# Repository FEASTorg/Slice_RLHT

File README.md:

# Sice RLHT

Relay Heating Element Controller Slice for BREAD.

## Introduction

[Provide a brief introduction to the project, including the motivation and goals. Explain the significance and context of the research.]

## Project Overview

[Describe the project in more detail. This section can be split into subsections if necessary.]

## Installation

[Provide instructions for installing any necessary software or hardware components.]

## Usage

[Explain how to use the project. Include examples and screenshots if applicable.]

### Basic Usage

[Provide basic usage instructions.]

### Advanced Usage

[Provide advanced usage instructions, including any optional features or configurations.]

## Documentation

[Link to the detailed documentation if available. Provide instructions on how to access and navigate the documentation.]

## Contributing

[Explain how others can contribute to the project. Include guidelines for submitting issues, pull requests, and any coding standards.]

### Code of Conduct

[Link to the project's code of conduct if available.]

## License

[State the license under which the project is distributed. Include a link to the full license text.]

## Acknowledgements

[Acknowledge any contributors, collaborators, funding sources, or organizations that supported the project.]

## Contact

[Provide contact information for the project maintainer(s) or lead researcher(s). Include an email address or a link to a contact form.]

---

<div align="center">
  
</div>

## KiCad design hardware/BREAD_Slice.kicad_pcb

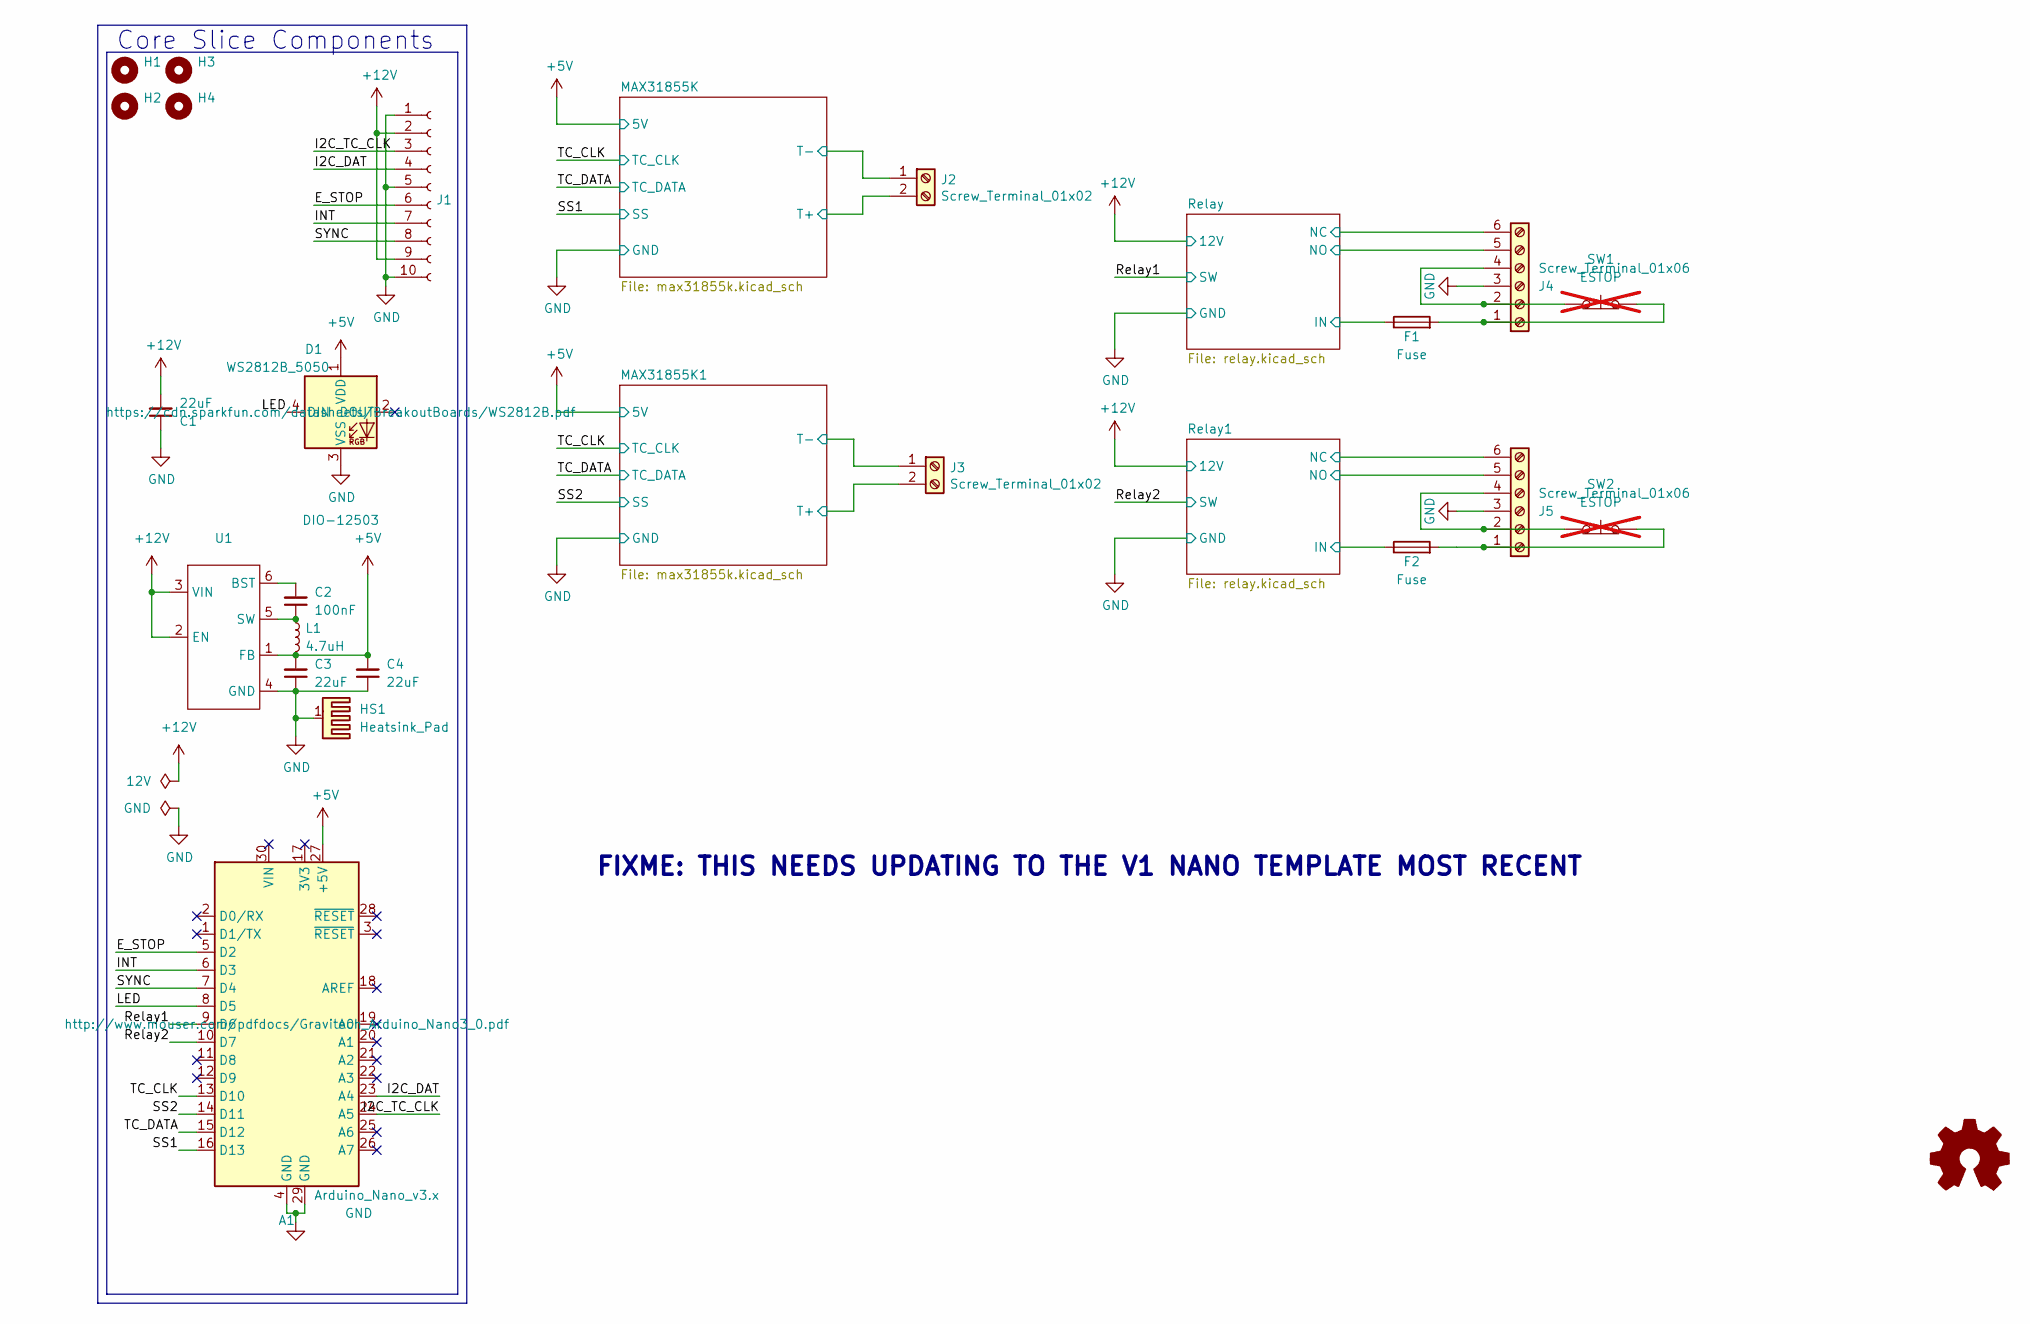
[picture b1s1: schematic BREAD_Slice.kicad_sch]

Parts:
A1: Arduino_Nano_v3.x; Arduino_Nano
C1, C3, C4: 22uF; C_1206_3216Metric
C2: 100nF; C_1206_3216Metric
D1: WS2812B_5050; WS2812-5050-4PIN
F1, F2: Fuse; Fuseholder_Clip-5x20mm_Bel_FC-203-22_Lateral_P17.80x5.00mm_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
H1, H2, H3, H4: MountingHole; MountingHole_5mm
HS1: Heatsink_Pad; Thermal_Pad
J1: Conn_01x10_Female; PinSocket_1x10_P2.54mm_Horizontal
J2, J3: Screw_Terminal_01x02; TerminalBlock_Phoenix_MPT-0,5-2-2.54_1x02_P2.54mm_Horizontal
J4, J5: Screw_Terminal_01x06; TerminalBlock_Phoenix_MKDS-1,5-6-5.08_1x06_P5.08mm_Horizont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
L1: 4.7uH; L_1210_3225Metric
SW1, SW2: ESTOP; not fitted
U1: SOIC_05WU-7_DIO

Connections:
+5V: A1.27 (+5V), C3.2, C4.2, D1.1 (VDD), L1.2, U1.1 (FB); also elsewhere on the board
+12V: C1.2, J1.2, J1.9, U1.2 (EN), U1.3 (VIN); also elsewhere on the board
/E_STOP: A1.5 (D2), J1.6
/I2C_DAT: A1.23 (A4), J1.4
/I2C_TC_CLK: A1.24 (A5), J1.3
/INT: A1.6 (D3), J1.7
/LED: A1.8 (D5), D1.4 (DIN)
/MAX31855K1/T+: J3.2; also elsewhere on the board
/MAX31855K1/T-: J3.1; also elsewhere on the board
/MAX31855K/T+: J2.2; also elsewhere on the board
/MAX31855K/T-: J2.1; also elsewhere on the board
/Relay1: A1.9 (D6); also elsewhere on the board
/Relay1/IN: F2.1; also elsewhere on the board
/Relay1/NC: J5.6; also elsewhere on the board
/Relay1/NO: J5.5; also elsewhere on the board
/Relay2: A1.10 (D7); also elsewhere on the board
/Relay/IN: F1.1; also elsewhere on the board
/Relay/NC: J4.6; also elsewhere on the board
/Relay/NO: J4.5; also elsewhere on the board
/SS1: A1.16 (D13); also elsewhere on the board
/SS2: A1.14 (D11); also elsewhere on the board
/SYNC: A1.7 (D4), J1.8
/TC_CLK: A1.13 (D10); also elsewhere on the board
/TC_DATA: A1.15 (D12); also elsewhere on the board
GND: A1.4 (GND), A1.29 (GND), C1.1, C3.1, C4.1, D1.3 (VSS), HS1.1, J1.1, J1.5, J1.10, J4.3, J5.3, U1.4 (GND); also elsewhere on the board
unnamed: F1.2, J4.1, SW1.2 (B)
unnamed: J4.2, J4.4, SW1.1 (A)
unnamed: F2.2, J5.1, SW2.2 (B)
unnamed: J5.2, J5.4, SW2.1 (A)
unnamed: C2.2, U1.6 (BST)
unnamed: C2.1, L1.1, U1.5 (SW)

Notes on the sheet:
FIXME: THIS NEEDS UPDATING TO THE V1 NANO TEMPLATE MOST RECENT
Core Slice Components

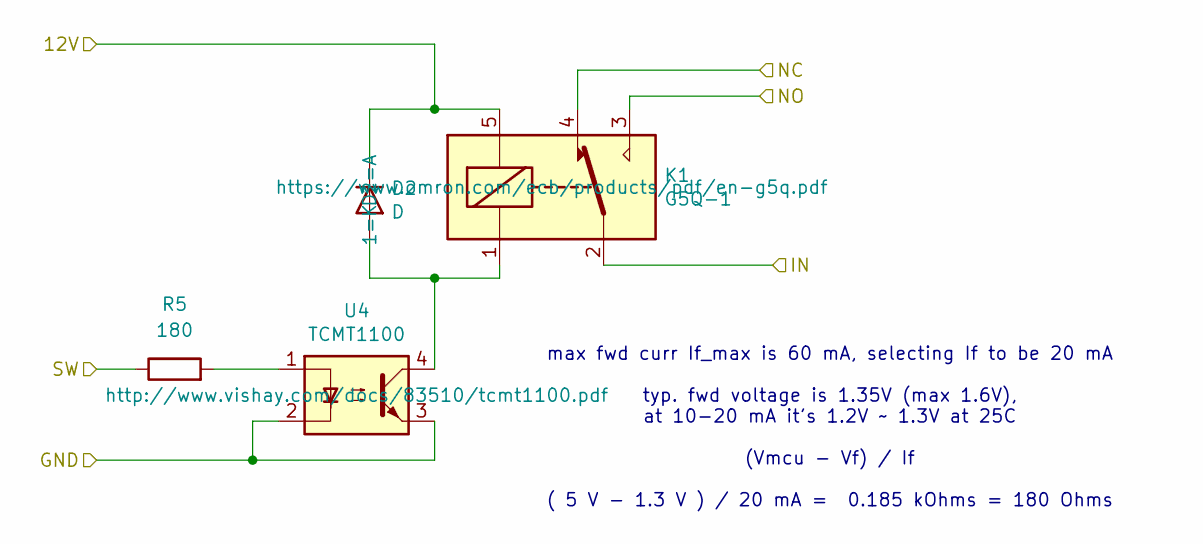
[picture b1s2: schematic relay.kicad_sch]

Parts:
D2: D; D_DO-35_SOD27_P7.62mm_Horizontal
K1: G5Q-1; Relay_SPDT_Omron-G5Q-1
R5: 180; R_1206_3216Metric_Pad1.30x1.75mm_HandSolder
U4: TCMT1100; SOP-4_4.4x2.6mm_P1.27mm

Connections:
+12V: D2.1 (K), K1.5; also elsewhere on the board
/Relay1: R5.1; also elsewhere on the board
/Relay/IN: K1.2; also elsewhere on the board
/Relay/NC: K1.4; also elsewhere on the board
/Relay/NO: K1.3; also elsewhere on the board
GND: U4.2, U4.3; also elsewhere on the board
unnamed: D2.2 (A), K1.1, U4.4
unnamed: R5.2, U4.1

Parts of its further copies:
D3: D; D_DO-35_SOD27_P7.62mm_Horizontal
K2: G5Q-1; Relay_SPDT_Omron-G5Q-1
R6: 180; R_1206_3216Metric_Pad1.30x1.75mm_HandSolder
U5: TCMT1100; SOP-4_4.4x2.6mm_P1.27mm

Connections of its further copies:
+12V: D3.1 (K), K2.5; also elsewhere on the board
/Relay1/IN: K2.2; also elsewhere on the board
/Relay1/NC: K2.4; also elsewhere on the board
/Relay1/NO: K2.3; also elsewhere on the board
/Relay2: R6.1; also elsewhere on the board
GND: U5.2, U5.3; also elsewhere on the board
unnamed: D3.2 (A), K2.1, U5.4
unnamed: R6.2, U5.1

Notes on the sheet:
max fwd curr If_max is 60 mA, selecting If to be 20 mA typ. fwd voltage is 1.35V (max 1.6V), at 10-20 mA it's 1.2V ~ 1.3V at 25C (Vmcu - Vf) / If ( 5 V - 1.3 V ) / 20 mA = 0.185 kOhms = 180 Ohms

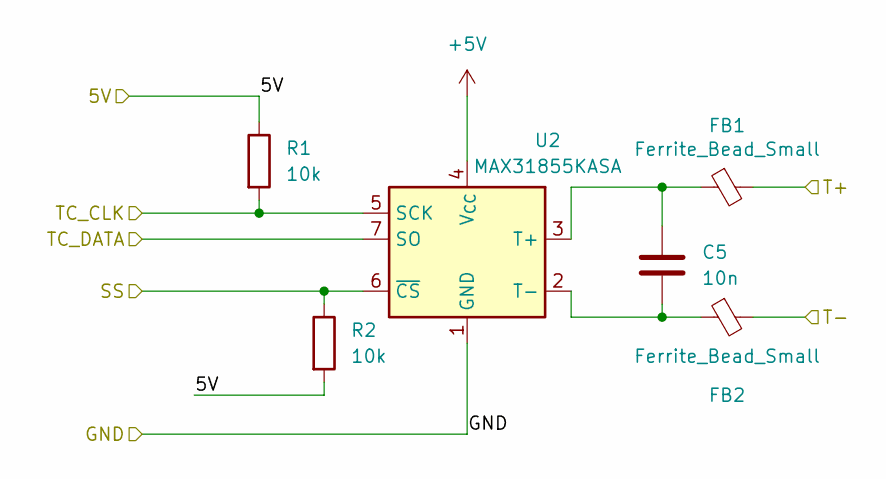
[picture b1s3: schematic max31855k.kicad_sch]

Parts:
C5: 10n; C_1206_3216Metric_Pad1.33x1.80mm_HandSolder
FB1, FB2: Ferrite_Bead_Small; R_1206_3216Metric_Pad1.30x1.75mm_HandSolder
R1, R2: 10k; R_1206_3216Metric_Pad1.30x1.75mm_HandSolder
U2: MAX31855KASA; SOIC-8_3.9x4.9mm_P1.27mm

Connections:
+5V: R1.1, R2.2, U2.4 (V_{CC}); also elsewhere on the board
/MAX31855K/T+: FB1.2; also elsewhere on the board
/MAX31855K/T-: FB2.2; also elsewhere on the board
/SS1: R2.1, U2.6 (~CS); also elsewhere on the board
/TC_CLK: R1.2, U2.5 (SCK); also elsewhere on the board
/TC_DATA: U2.7 (SO); also elsewhere on the board
GND: U2.1 (GND); also elsewhere on the board
unnamed: C5.1, FB1.1, U2.3 (T+)
unnamed: C5.2, FB2.1, U2.2 (T-)

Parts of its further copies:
C6: 10n; C_1206_3216Metric_Pad1.33x1.80mm_HandSolder
FB3, FB4: Ferrite_Bead_Small; R_1206_3216Metric_Pad1.30x1.75mm_HandSolder
R3, R4: 10k; R_1206_3216Metric_Pad1.30x1.75mm_HandSolder
U3: MAX31855KASA; SOIC-8_3.9x4.9mm_P1.27mm

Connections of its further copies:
+5V: R3.1, R4.2, U3.4 (V_{CC}); also elsewhere on the board
/MAX31855K1/T+: FB3.2; also elsewhere on the board
/MAX31855K1/T-: FB4.2; also elsewhere on the board
/SS2: R4.1, U3.6 (~CS); also elsewhere on the board
/TC_CLK: R3.2, U3.5 (SCK); also elsewhere on the board
/TC_DATA: U3.7 (SO); also elsewhere on the board
GND: U3.1 (GND); also elsewhere on the board
unnamed: C6.1, FB3.1, U3.3 (T+)
unnamed: C6.2, FB4.1, U3.2 (T-)

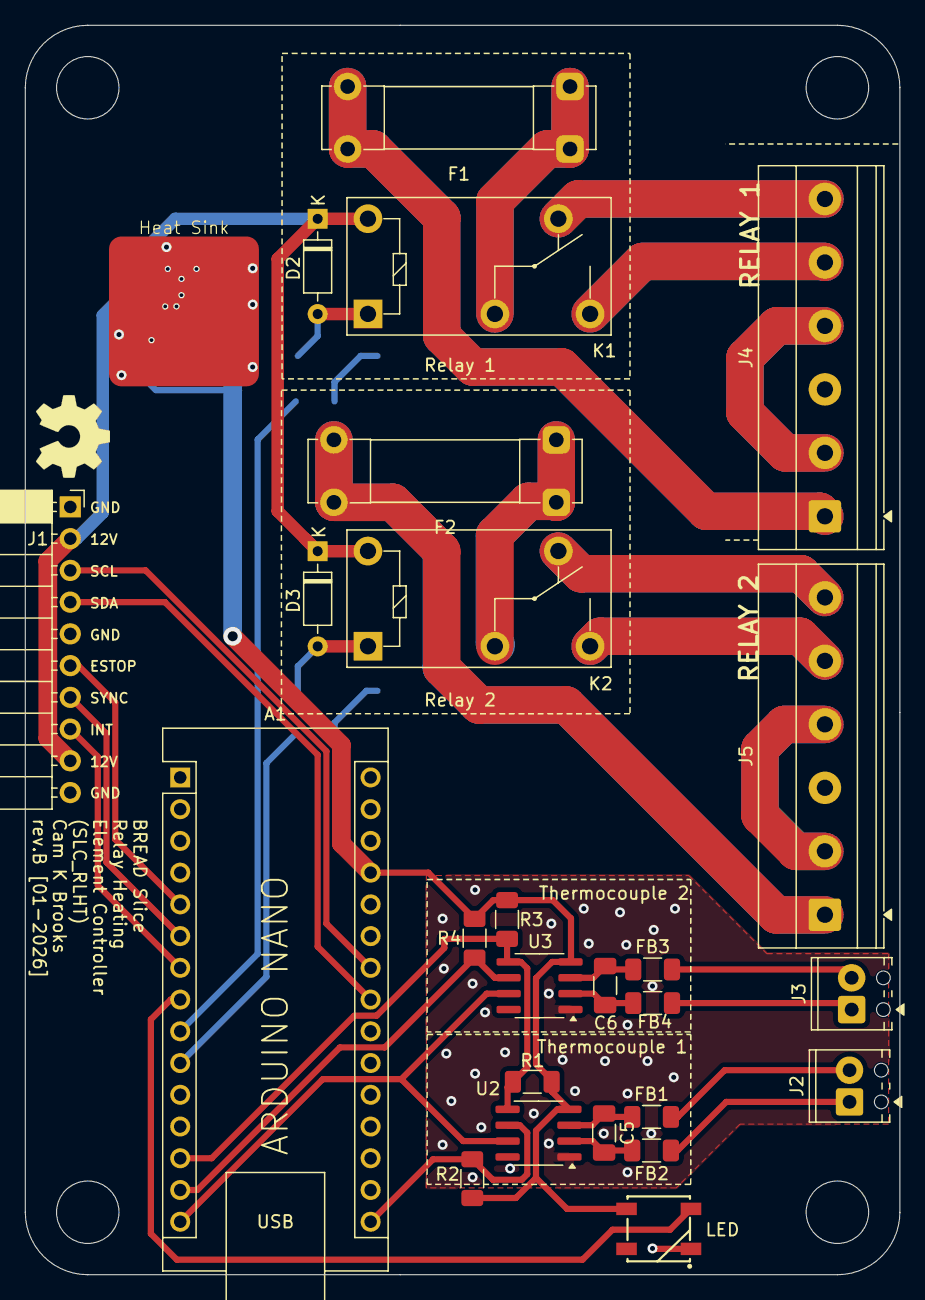
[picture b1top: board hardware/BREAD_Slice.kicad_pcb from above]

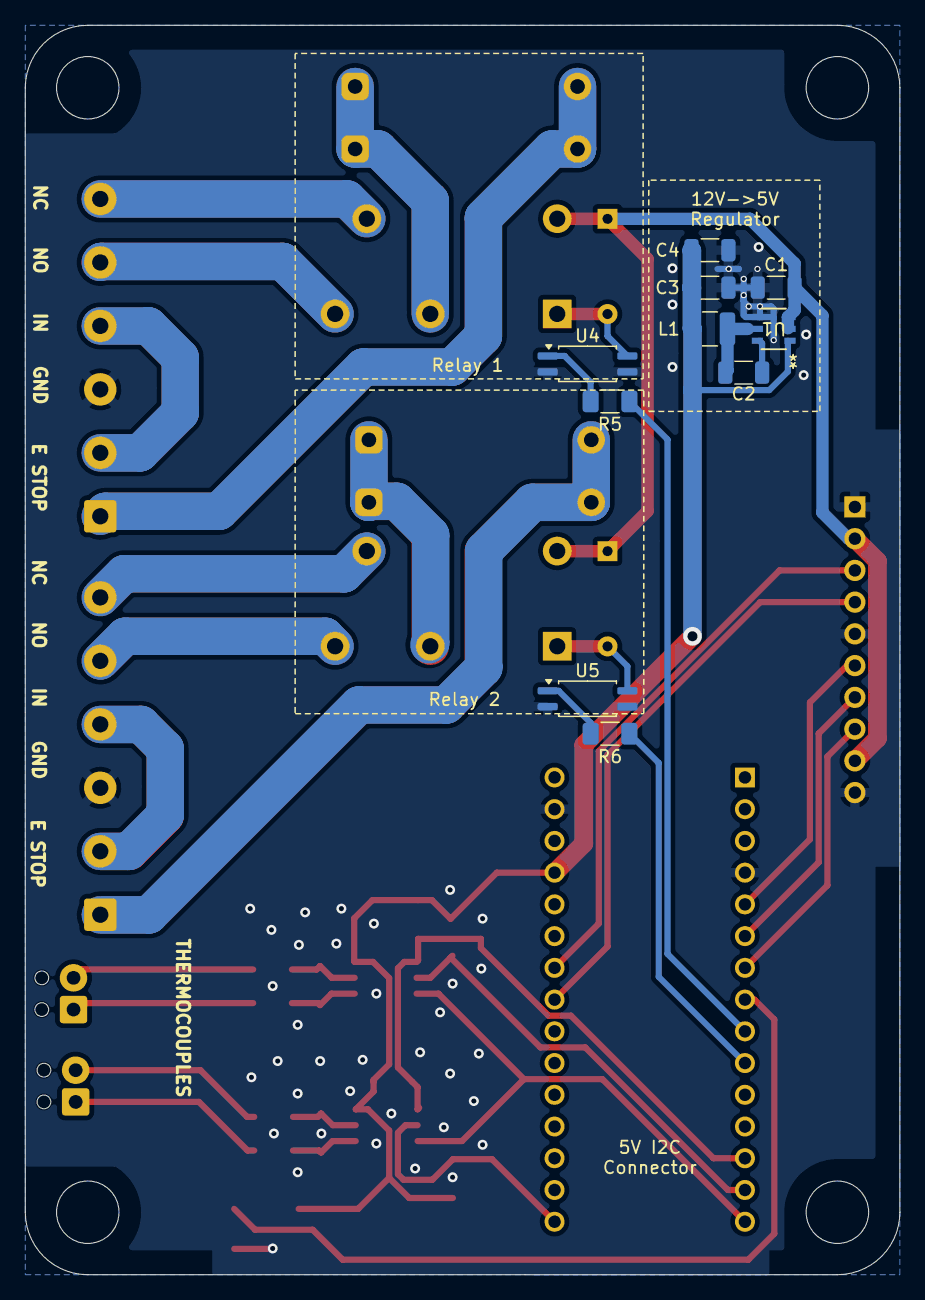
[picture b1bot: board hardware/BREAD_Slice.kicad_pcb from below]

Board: 2 copper layers, 70.0 x 100.0 mm, 41 parts (10 on the bottom side), 39 nets.

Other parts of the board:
Logo1: Logo_Open_Hardware_Small; OSHW-Symbol_6.7x6mm_SilkScreen

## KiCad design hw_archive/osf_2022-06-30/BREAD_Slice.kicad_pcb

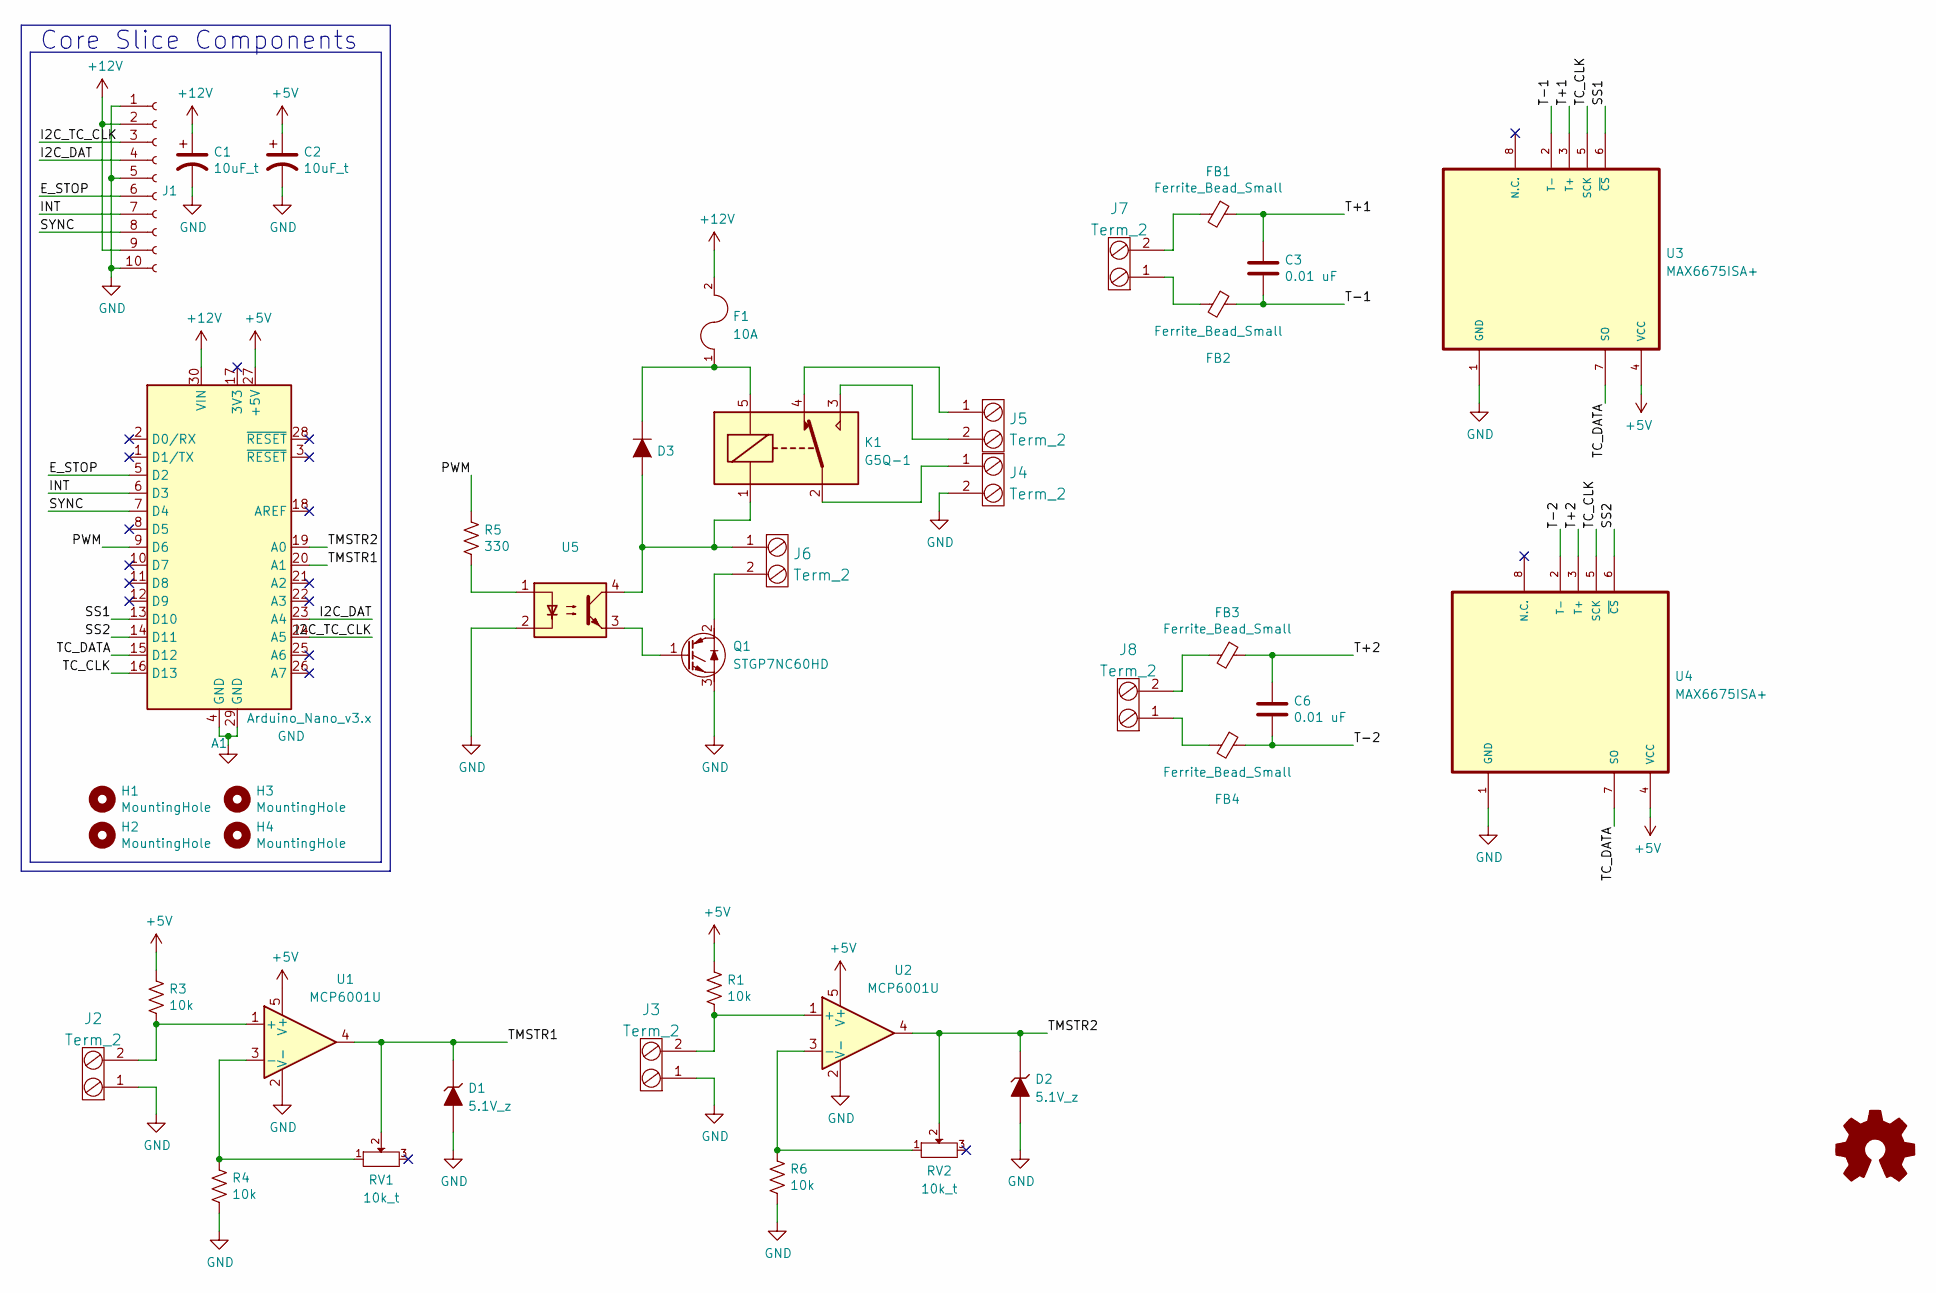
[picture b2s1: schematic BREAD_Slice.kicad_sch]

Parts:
A1: Arduino_Nano_v3.x; Arduino_Nano
C1, C2: 10uF_t; C_1206_HandSoldering; Part # T491C106K025AT
C3, C6: 0.01 uF; C_1206_HandSoldering
D1, D2: 5.1V_z; Diode_DO-41_SOD81_Horizontal_RM10; Part # 1N4733ATR
D3: General_Purpose_Diode; Diode_DO-201AD_Horizontal_RM15; Part # 1N914BWS
F1: 10A; Fuse_Holder; Part # 3522-2
FB1, FB2, FB3, FB4: Ferrite_Bead_Small; R_1206_HandSoldering
H1, H2, H3, H4: MountingHole; MountingHole_3.2mm_M3_DIN965_Pad
J1: Conn_01x10_Female; PinSocket_1x10_P2.54mm_Horizontal
J2, J3, J4, J5, J6, J7, J8: Term_2; TerminalBlock_Pheonix_MKDS1.5-2pol; Part # 1935161
K1: G5Q-1; Relay_SPDT_Omron-G5Q-1
Logo1: Logo_Open_Hardware_Small; OSHW-Symbol_6.7x6mm_SilkScreen
Q1: STGP7NC60HD; TO-220-3_Vertical
R1, R3, R4, R6: 10k; R_1206_HandSoldering
R5: 330; R_1206_HandSoldering
RV1, RV2: 10k_t; Potentiometer_Bourns_3296W_3-8Zoll_Inline_ScrewUp; Part # 1-1623849-0
U1, U2: MCP6001U; SOT-23-5
U3, U4: MAX6675ISA+; SOIC127P600X175-8N
U5: (no value)

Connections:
+5V: A1.27 (+5V), C2.1, R1.1, R3.1, U1.5 (V+), U2.5 (V+), U3.4 (VCC), U4.4 (VCC)
+12V: A1.30 (VIN), C1.1, F1.2, J1.2, J1.9
/E_STOP: A1.5 (D2), J1.6
/I2C_DAT: A1.23 (A4), J1.4
/I2C_TC_CLK: A1.24 (A5), J1.3
/INT: A1.6 (D3), J1.7
/PWM: A1.9 (D6), R5.1
/SS1: A1.13 (D10), U3.6 (~CS)
/SS2: A1.14 (D11), U4.6 (~CS)
/SYNC: A1.7 (D4), J1.8
/T+1: C3.1, FB1.1, U3.3 (T+)
/T+2: C6.1, FB3.1, U4.3 (T+)
/T-1: C3.2, FB2.1, U3.2 (T-)
/T-2: C6.2, FB4.1, U4.2 (T-)
/TC_CLK: A1.16 (D13), U3.5 (SCK), U4.5 (SCK)
/TC_DATA: A1.15 (D12), U3.7 (SO), U4.7 (SO)
/TMSTR1: A1.20 (A1), D1.1 (K), RV1.2, U1.4
/TMSTR2: A1.19 (A0), D2.1 (K), RV2.2, U2.4
GND: A1.4 (GND), A1.29 (GND), C1.2, C2.2, D1.2 (A), D2.2 (A), J1.1, J1.5, J1.10, J2.1, J3.1, J4.2, Q1.3 (E), R4.2, R6.2, U1.2 (V-), U2.2 (V-), U3.1 (GND), U4.1 (GND), U5.2
unnamed: D3.1 (K), F1.1, K1.5
unnamed: D3.2 (A), J6.1, K1.1, U5.4
unnamed: FB1.2, J7.2
unnamed: FB2.2, J7.1
unnamed: FB3.2, J8.2
unnamed: FB4.2, J8.1
unnamed: J2.2, R3.2, U1.1 (+)
unnamed: J3.2, R1.2, U2.1 (+)
unnamed: J4.1, K1.2
unnamed: J5.1, K1.4
unnamed: J5.2, K1.3
unnamed: J6.2, Q1.2 (C)
unnamed: Q1.1 (G), U5.3
unnamed: R4.1, RV1.1, U1.3 (-)
unnamed: R5.2, U5.1
unnamed: R6.1, RV2.1, U2.3 (-)

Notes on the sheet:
Core Slice Components

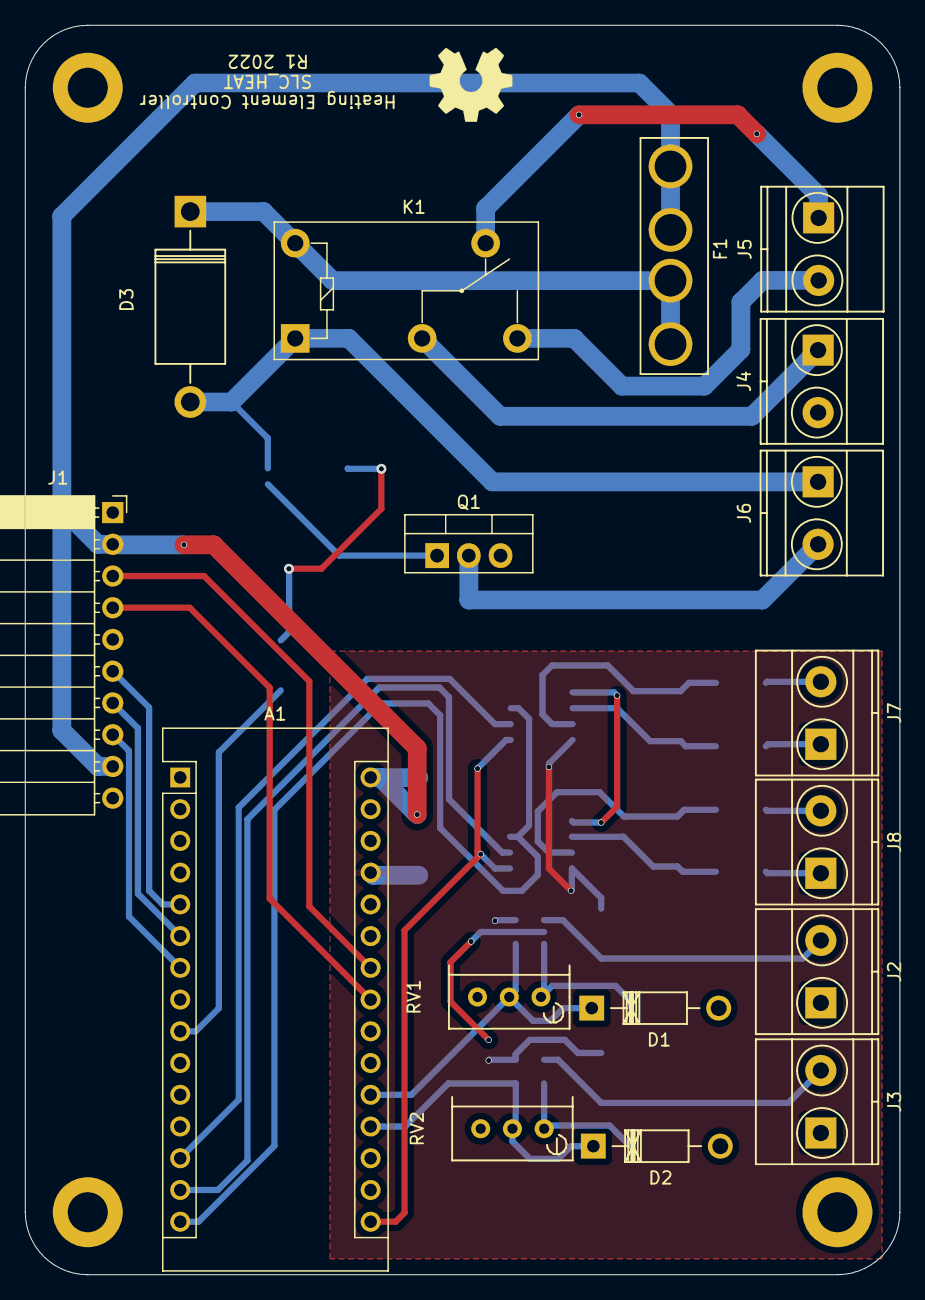
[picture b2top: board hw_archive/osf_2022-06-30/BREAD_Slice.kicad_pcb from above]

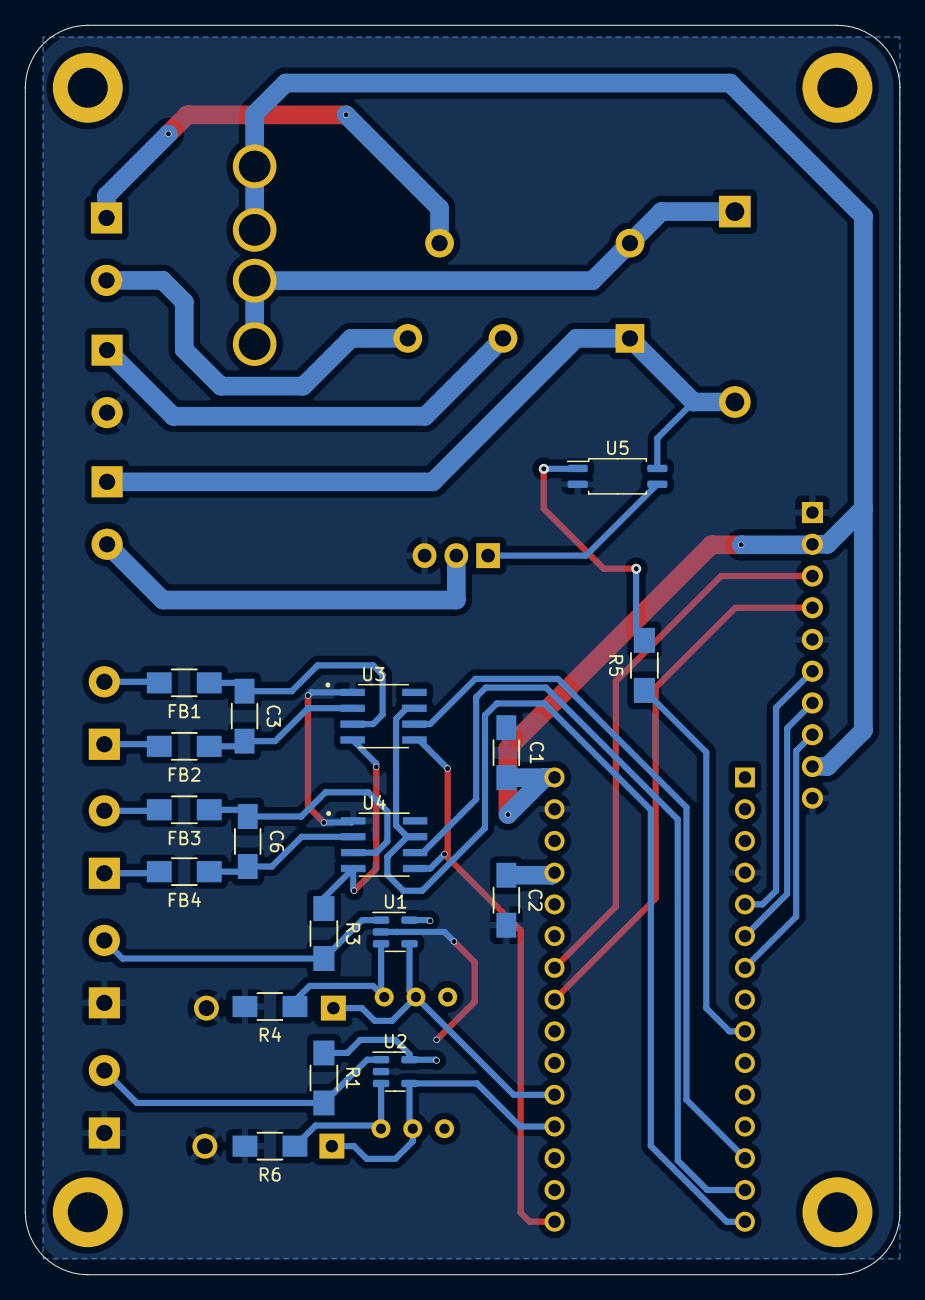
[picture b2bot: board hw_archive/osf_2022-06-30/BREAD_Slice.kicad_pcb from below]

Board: 2 copper layers, 70.0 x 100.0 mm, 40 parts (18 on the bottom side), 35 nets.

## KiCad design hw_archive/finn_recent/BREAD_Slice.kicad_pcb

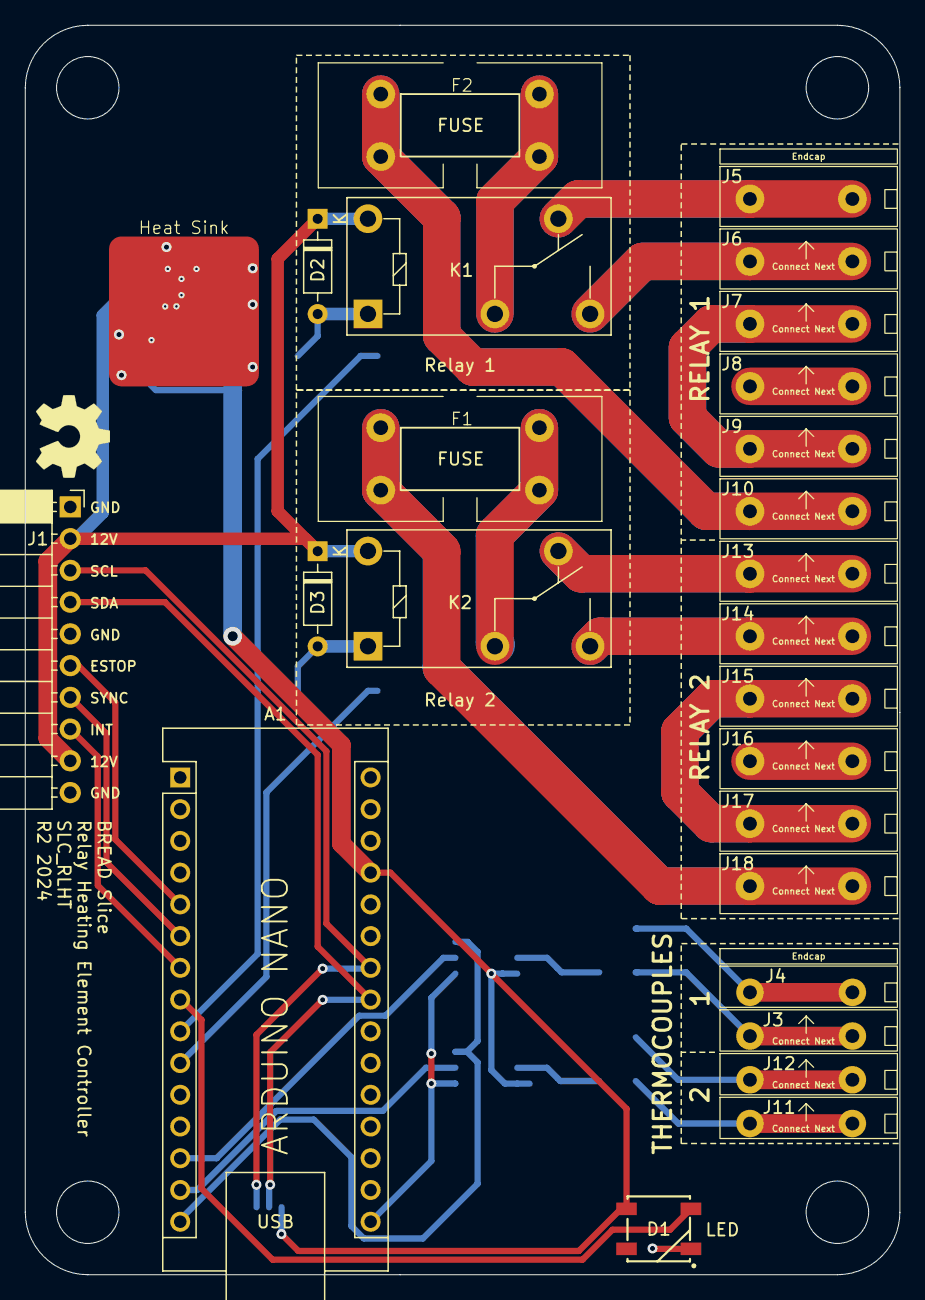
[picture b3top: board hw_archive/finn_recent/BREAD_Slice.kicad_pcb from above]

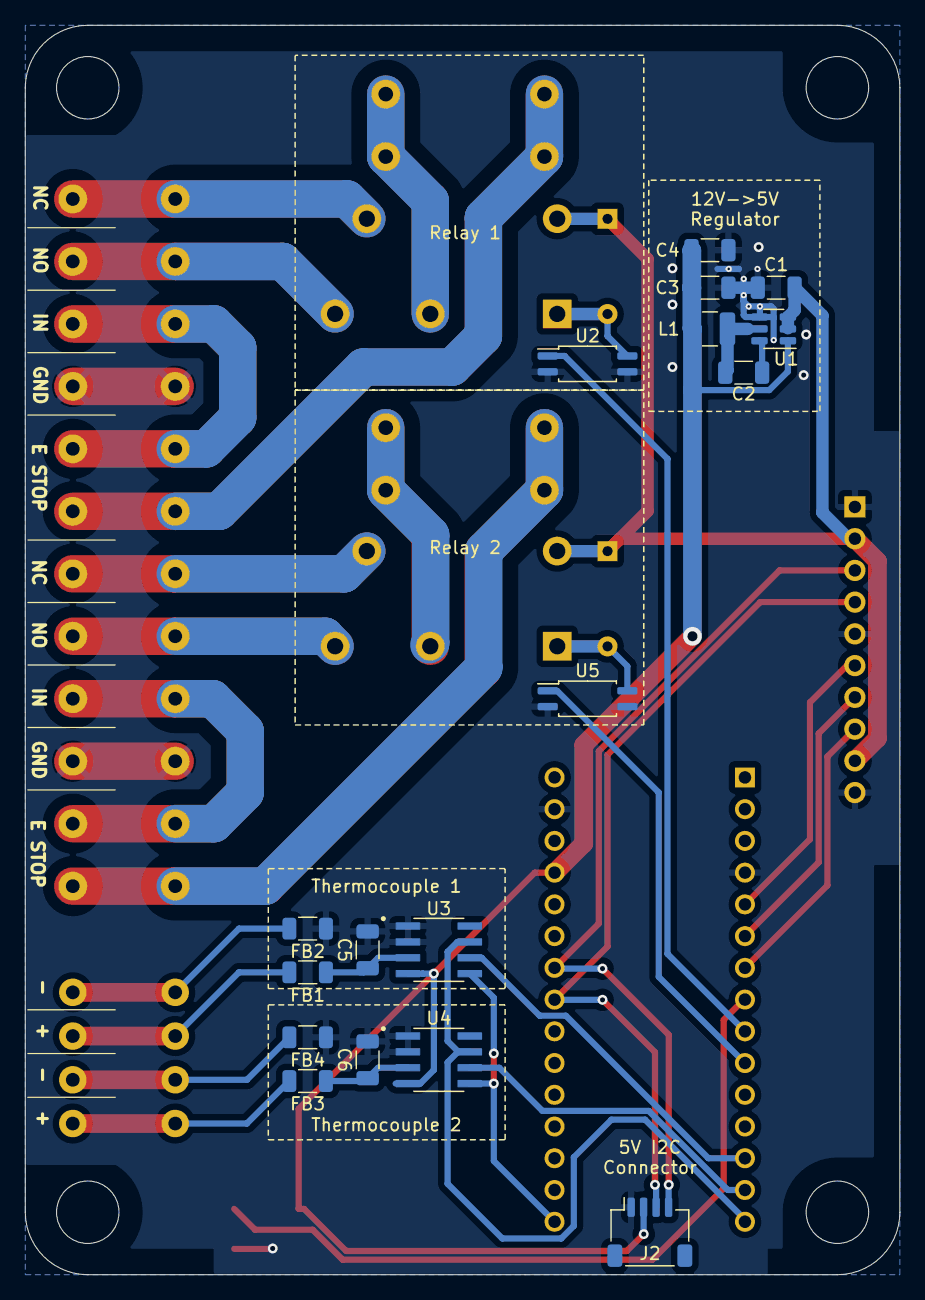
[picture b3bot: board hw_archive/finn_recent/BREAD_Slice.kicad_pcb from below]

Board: 2 copper layers, 70.0 x 100.0 mm, 48 parts (17 on the bottom side), 35 nets.

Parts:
A1: Arduino_Nano_v3.x; Arduino_Nano
C1, C3, C4: 22uF; C_1206_3216Metric
C2: 100nF; C_1206_3216Metric
C5, C6: 0.01 uF; C_1206_3216Metric
D1: WS2812B_5050; WS2812-5050-4PIN
D2, D3: General_Purpose_Diode; D_DO-35_SOD27_P7.62mm_Horizontal
F1, F2: 10A; Glass Fuse Clip 5x20MM
FB1, FB2, FB3, FB4: Ferrite_Bead_Small; R_1206_3216Metric
H1, H2, H3, H4: MountingHole; MountingHole_5mm
HS1: Heatsink_Pad; Thermal Pad
J1: Conn_01x10_Female; PinSocket_1x10_P2.54mm_Horizontal
J2: I2C_01x04; JST_SH_SM04B-SRSS-TB_1x04-1MP_P1.00mm_Horizontal
J3, J11, J12: Term_PressFit_Phoenix_Contact; Term_PressFit_3.5mm_H_PC
J4: Term_PressFit_Phoenix_Contact; Term_PressFit_3.5mm_H_ENDCAP_PC
J5: Term_PressFit_Phoenix_Contact; Term_PressFit_5mm_H_ENDCAP_PC_HVRELAY
J6, J7, J8, J9, J10, J13, J14, J15, J16, J17, J18: Term_PressFit_Phoenix_Contact; Term_PressFit_5mm_H_PC_HVRELAY
K1, K2: G5Q-1; Relay_SPDT_Omron-G5Q-1
L1: 4.7uH; L_1210_3225Metric
Logo1: Logo_Open_Hardware_Small; OSHW-Symbol_6.7x6mm_SilkScreen
U1: TSOT-23-6
U2, U5: TCMT1100; SOP-4_4.4x2.6mm_P1.27mm
U3, U4: MAX6675ISA+; SOIC127P600X175-8N

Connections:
+5V: A1.27 (+5V), C3.2, C4.2, D1.1 (VDD), J2.2, L1.2, U1.1 (FB), U3.4 (VCC), U4.4 (VCC)
+12V: C1.2, D2.1 (K), D3.1 (K), J1.2, J1.9, K1.5, K2.5, U1.2 (EN), U1.3 (VIN)
/E_STOP: A1.5 (D2), J1.6
/I2C_DAT: A1.23 (A4), J1.4, J2.3
/I2C_TC_CLK: A1.24 (A5), J1.3, J2.4
/INT: A1.6 (D3), J1.7
/LED: A1.8 (D5), D1.4 (DIN)
/Relay1: A1.9 (D6), U2.1
/Relay2: A1.10 (D7), U5.1
/SS1: A1.13 (D10), U3.6 (~CS)
/SS2: A1.14 (D11), U4.6 (~CS)
/SYNC: A1.7 (D4), J1.8
/T+1: C5.1, FB1.1, U3.3 (T+)
/T+2: C6.1, FB3.1, U4.3 (T+)
/TC_CLK: A1.16 (D13), U3.5 (SCK), U4.5 (SCK)
/TC_DATA: A1.15 (D12), U3.7 (SO), U4.7 (SO)
ESTOP1: F2.1, J10.1
ESTOP2: F1.1, J18.1
FUSE1: F2.2, K1.2
FUSE2: F1.2, K2.2
GND: A1.4 (GND), A1.29 (GND), C1.1, C3.1, C4.1, C5.2, C6.2, D1.3 (VSS), FB2.1, FB4.1, HS1.1, J1.1, J1.5, J1.10, J2.1, J8.1, J16.1, U1.4 (GND), U2.2, U2.3, U3.1 (GND), U3.2 (T-), U4.1 (GND), U4.2 (T-), U5.2, U5.3
IN1: J7.1, J9.1
IN2: J15.1, J17.1
NC1: J5.1, K1.4
NC2: J13.1, K2.4
NO1: J6.1, K1.3
NO2: J14.1, K2.3
unnamed: D2.2 (A), K1.1, U2.4
unnamed: D3.2 (A), K2.1, U5.4
unnamed: FB1.2, J3.1
unnamed: FB2.2, J4.1
unnamed: FB3.2, J11.1
unnamed: FB4.2, J12.1
unnamed: C2.2, U1.6 (BST)
unnamed: C2.1, L1.1, U1.5 (SW)

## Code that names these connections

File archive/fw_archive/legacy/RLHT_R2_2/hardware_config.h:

#ifndef HARDWARE_CONFIG_H
#define HARDWARE_CONFIG_H

// General BREAD
#define ESTOP 2
#define LED_PIN 5

// RLHT Specific
#define TC_CS1 10 
#define TC_CS2 11
#define TC_DATA 12
#define TC_CLK 13

#define RELAY1 6
#define RELAY2 7

#endif // HARDWARE_CONFIG_H

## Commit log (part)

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2024-07-09 added firmware
2024-09-13 updated to have new terminals and review
2024-09-30 JLCPCB order rev-A
2025-02-20 added all revs of firmware and started iteration R2 new
2025-02-20 added historical hardware
2025-02-20 finalized modes addition
2025-02-20 added notes on hardware progression
2025-02-27 updated sketch
2025-03-06 added historical scripts and new revisions
2025-03-07 started merging in CRUMBs lib with slice hw
2025-03-07 updated crumbs sketch, got working with all commands
2025-03-07 fixed estop isr
2025-03-07 sectioned off estop logic from loop
2025-03-07 sectioned off setup and loop
2025-03-08 redid data structs
2025-03-16 updated sketch to use with dcmt rebuild
2025-03-16 modularized relay actuation function
2025-03-16 minor tweak
2025-03-16 moved debug macros to config
2025-04-19 minor tweaks
2025-09-17 change type id
2025-09-25 remove old hardware backups, they exist remotely
2025-09-25 move hardware archive to top level and consistent with DCMT
2025-09-25 ci: add bread-infra pipeline and all docs template files; also some reorganizing
2025-09-25 📄 KiBot index + board renders (auto)
2025-10-16 rename with generations and version numbers on firmware
2026-01-22 add legacy code for v1
2026-02-01 review and revise for current template and kmlib; still needs updating
2026-02-01 update todo
2026-03-09 chore: clean out readme tempalte
2026-03-09 chore: rearrange archives
2026-03-09 working ignore
2026-03-10 feat: clean cut over to new crumbs
2026-03-10 feat: add gen1/2 split in fw env
2026-03-10 hardening: add checks for dev context and version checks
2026-03-10 feat: add local shared header in prep for shared contract repo
2026-03-14 feat: use published contracts
2026-03-14 add effectively inert caps reply
2026-03-14 clean out legacy code after new contract cutover
2026-03-14 add i2c address selection from ini
2026-03-15 add base env for nano vs nano every
2026-03-15 add gitignore and extensions to firmware
2026-03-18 feat: make crumbs debug flag via build config
2026-03-18 remove duplicate print macro and clean up string hanlding
2026-03-18 internalize crumbs context
2026-03-18 add global decs. for PIDTunings
2026-03-18 tighten type to unsigned on relayPeriod and centralized period writer
2026-03-19 debounce estop and change to input pullup
2026-03-19 none: bump contracts (dcmt related update)
2026-03-19 add back version, idk how that happened
2026-03-19 add gitattributes to normalzie across platforms
2026-03-19 pollEStop() now uses a static CRGB lastLed = CRGB::Black local to gate FastLED.show() to transitions only
2026-03-19 use contract enums and cast
2026-03-19 remove duplicate (drift prone) version in favour of the canonical version defined in contract
2026-03-19 fix: thermocouple timing drift by using relative interval updates and replace raw INT16_MIN sentinel with protocol-defined BREAD_INVALID_I16
2026-04-02 chore: bump contracts (0.4.1) and crumbs (0.12.0) versions
2026-04-20 refactor: org casing rename from 'FEASTorg' to 'feastorg'
2026-05-12 feat(fw): add watchdog timer with 1s timeout
2026-05-12 fix(fw): protect shared state with interrupt guards
    Defer setRelayPeriod side-effects to main loop (PID not ISR-safe).
    Snapshot ISR-written command fields atomically in relayControlLogic.
    Add noInterrupts/interrupts guards in processEStop writes.
2026-05-12 fix(fw): replace String with static buffer in serial commands
    Eliminates all heap allocations from the serial command parser.
    Uses a 64-byte static char buffer and C string functions (atol,
    atof, strcmp_P) to prevent heap fragmentation on long-running
    ATmega328 devices.
2026-05-12 fix(fw): use unsigned long for timing fields
    Matches millis() return type, prevents signed overflow after ~24 days.
2026-05-12 fix(fw): guard empty string trim, remove no-op relay commit
2026-05-17 add retrospective changelog
2026-05-17 revise changelog for consistency
2026-05-20 Add slice.yaml manifest (schema v1.0 pilot)
2026-05-20 Add CI workflow with manifest validation
2026-05-24 Add standardized TODO.md with Pass 1/Pass 2 structure
2026-06-11 chore: update crumbs contract dependencies
2026-06-11 ci: retrigger after schema-v1.0 tag creation
2026-06-11 chore: update crumbs contract dependencies (#1)
    * chore: update crumbs contract dependencies
    * ci: retrigger after schema-v1.0 tag creation
